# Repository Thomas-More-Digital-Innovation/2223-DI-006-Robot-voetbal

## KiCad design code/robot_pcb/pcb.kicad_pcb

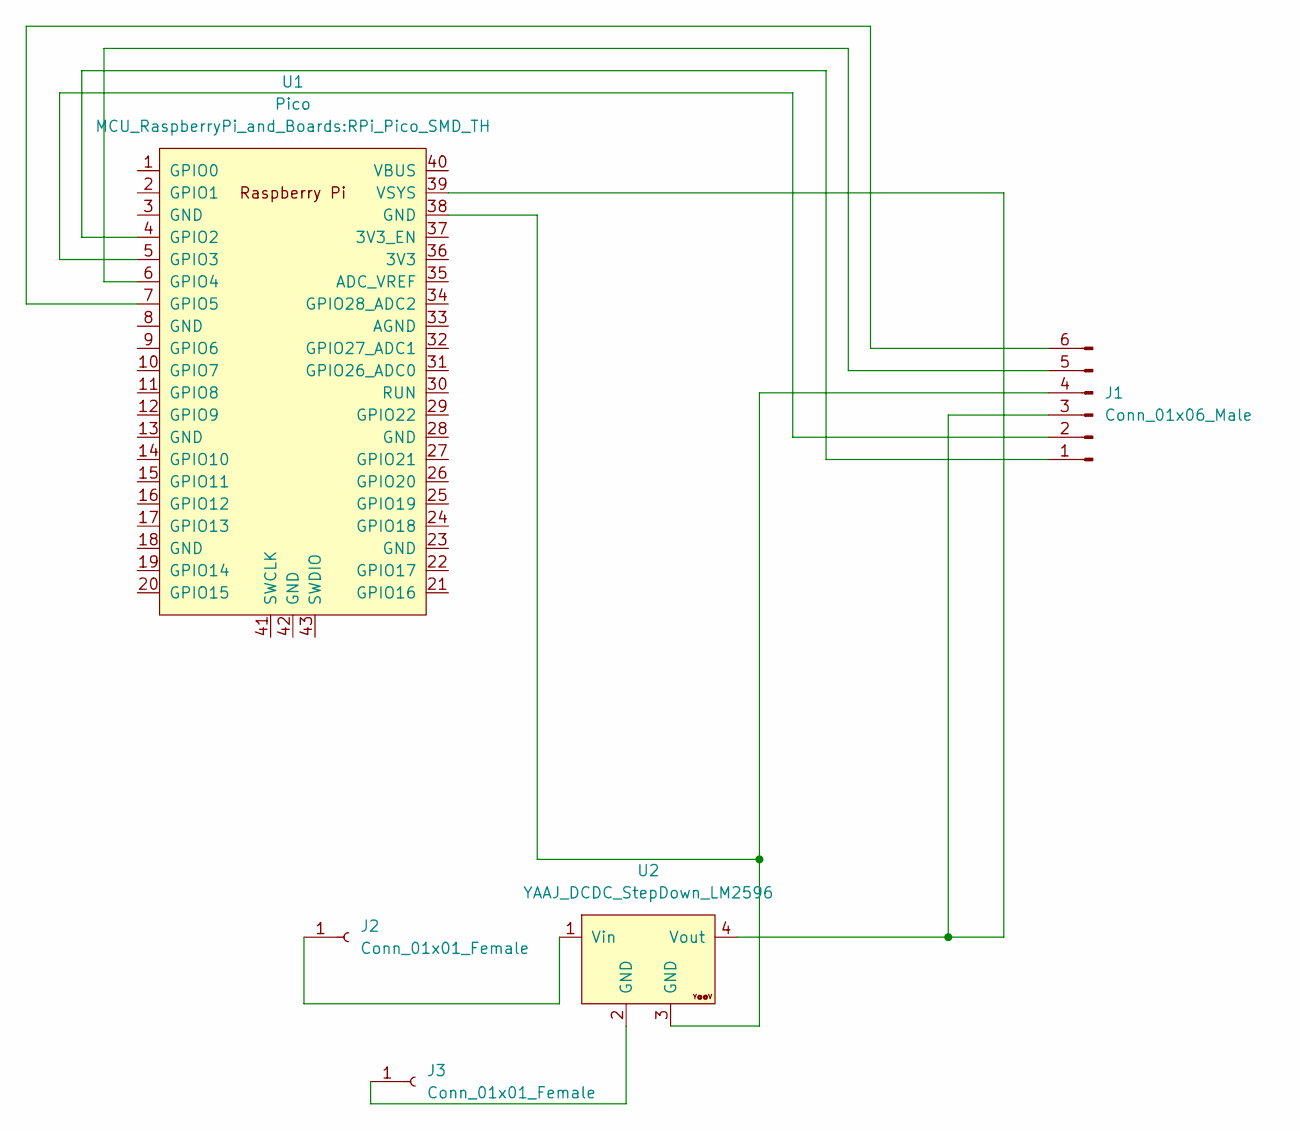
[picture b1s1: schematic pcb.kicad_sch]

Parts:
J1: Conn_01x06_Male; PinHeader_1x06_P1.00mm_Horizontal
J2, J3: Conn_01x01_Female; PinSocket_1x01_P2.00mm_Vertical
U1: Pico; RPi_Pico_SMD_TH
U2: YAAJ_DCDC_StepDown_LM2596

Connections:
unnamed: J1.1, U1.4 (GPIO2)
unnamed: J1.2, U1.5 (GPIO3)
unnamed: J1.3, U1.39 (VSYS), U2.4 (Vout)
unnamed: J1.4, U1.38 (GND), U2.3 (GND)
unnamed: J1.5, U1.6 (GPIO4)
unnamed: J1.6, U1.7 (GPIO5)
unnamed: J2.1, U2.1 (Vin)
unnamed: J3.1, U2.2 (GND)

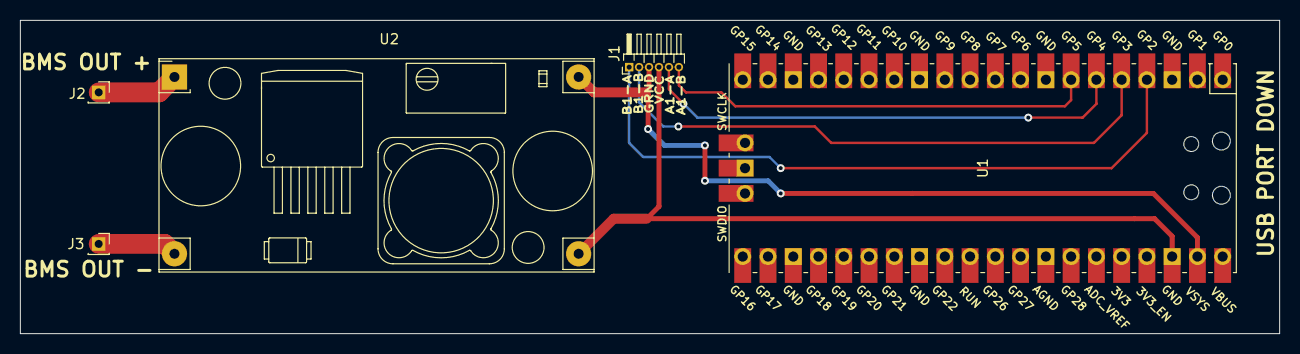
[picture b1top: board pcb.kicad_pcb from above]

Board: 2 copper layers, 126.6 x 31.5 mm, 5 parts (0 on the bottom side), 8 nets.

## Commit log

2022-10-19 first push of opencv detection script
2022-10-19 added .gitignore
2022-10-20 added more structure and small features
2022-10-21 better car position filter
2022-10-21 added ball tracking and mask filter trouble shooting
2022-11-18 added training env
2022-11-18 rename dir
2022-11-25 big change
2022-11-28 changed README
2022-12-08 added singleton design pattern
2022-12-08 Added Signleton design pattern
2023-01-12 Added the robot controller, the robot software itself, and the pcb design for future reference
2023-01-14 update to controlleer, and robot code
